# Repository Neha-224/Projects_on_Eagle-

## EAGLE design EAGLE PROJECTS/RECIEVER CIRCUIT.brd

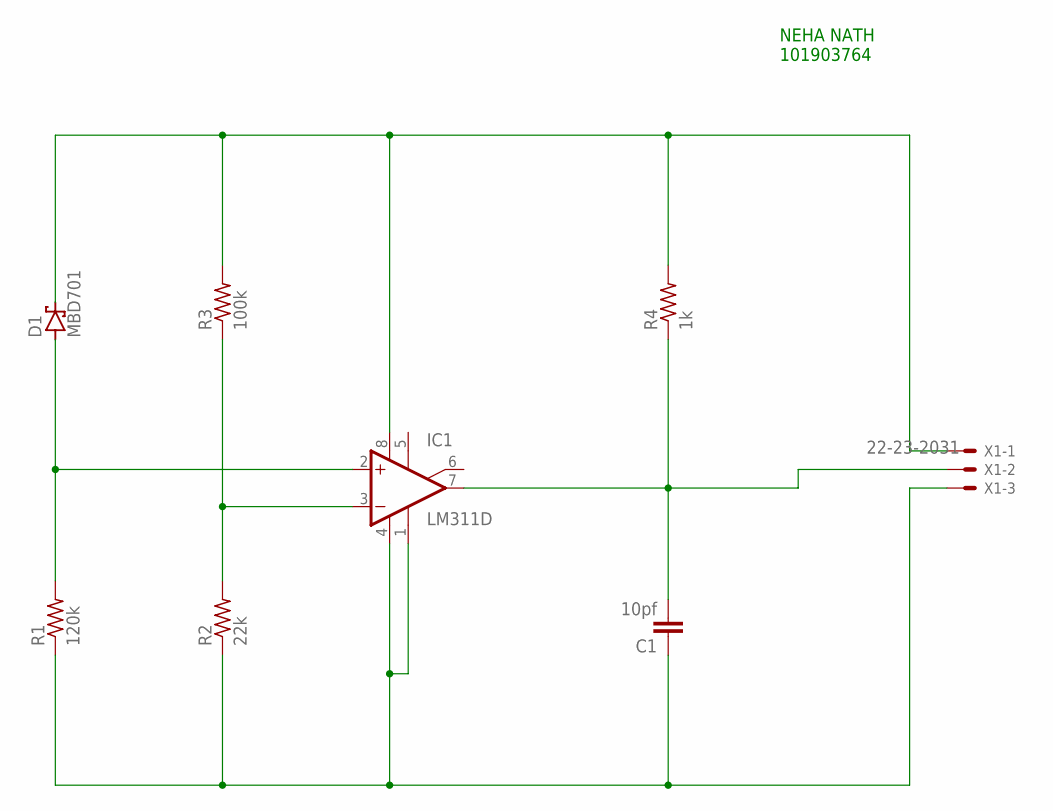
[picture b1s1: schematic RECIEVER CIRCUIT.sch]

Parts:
C1: 10pf; C2.5-4
D1: MBD701; TO92H
IC1: LM311D; SO08
R1: 120k; 0207/15
R2: 22k; 0207/15
R3: 100k; 0207/15
R4: 1k; 0207/15
X1: 22-23-2031

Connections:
unnamed: D1.2 (C), IC1.8 (V+), R3.2, R4.2, X1.1
unnamed: C1.1, IC1.1 (GND), IC1.4 (V-), R1.1, R2.1, X1.3
unnamed: D1.1 (A), IC1.2 (+IN), R1.2
unnamed: IC1.3 (-IN), R2.2, R3.1
unnamed: C1.2, IC1.7 (OUT), R4.1, X1.2

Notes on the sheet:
NEHA NATH 101903764

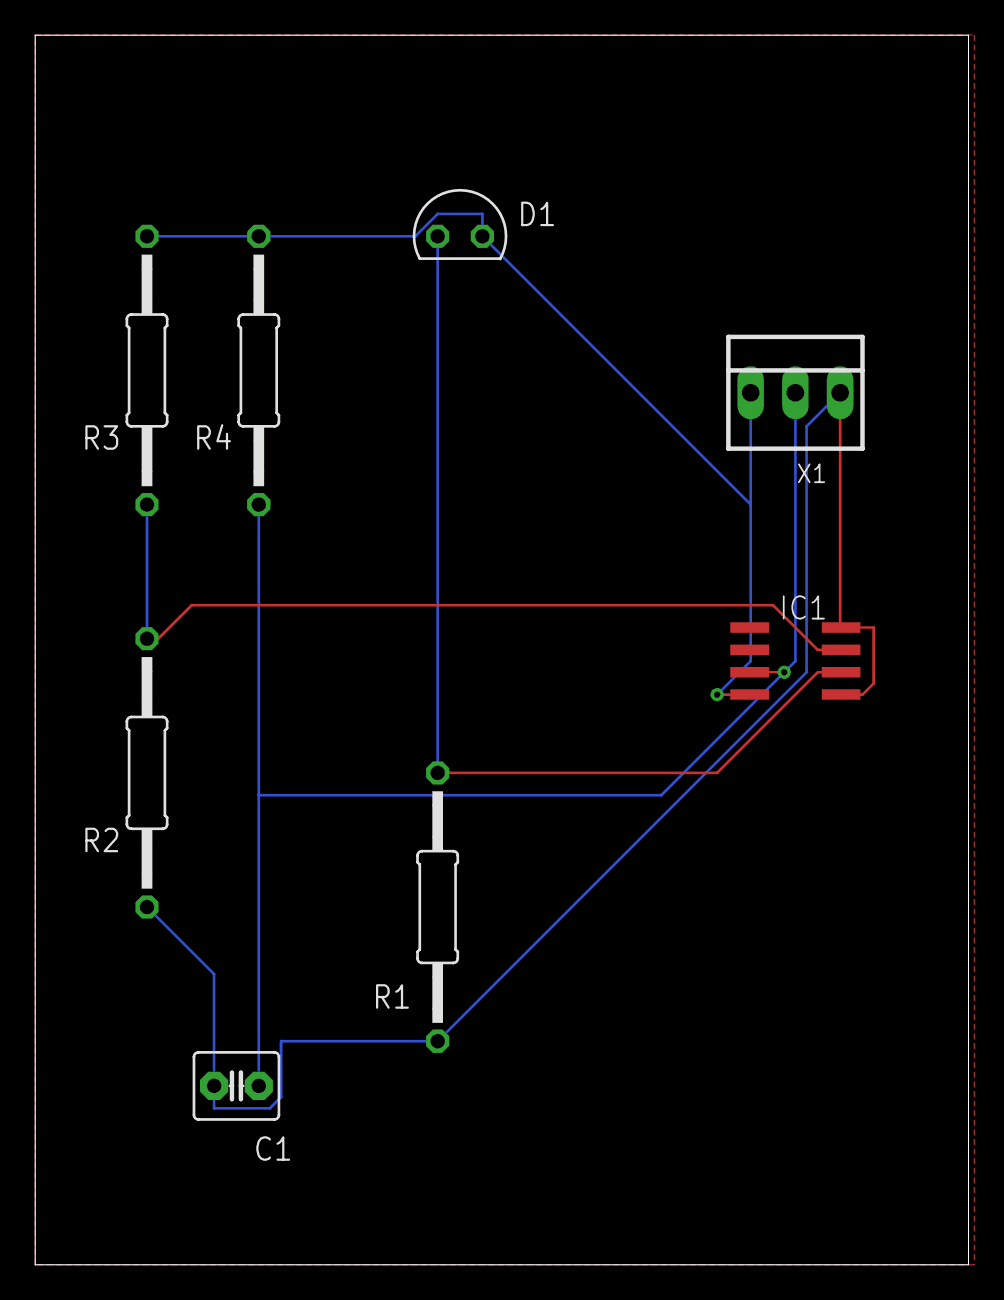
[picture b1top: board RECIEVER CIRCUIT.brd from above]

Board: 2 copper layers, 53.0 x 69.8 mm, 8 parts (0 on the bottom side), 5 nets.

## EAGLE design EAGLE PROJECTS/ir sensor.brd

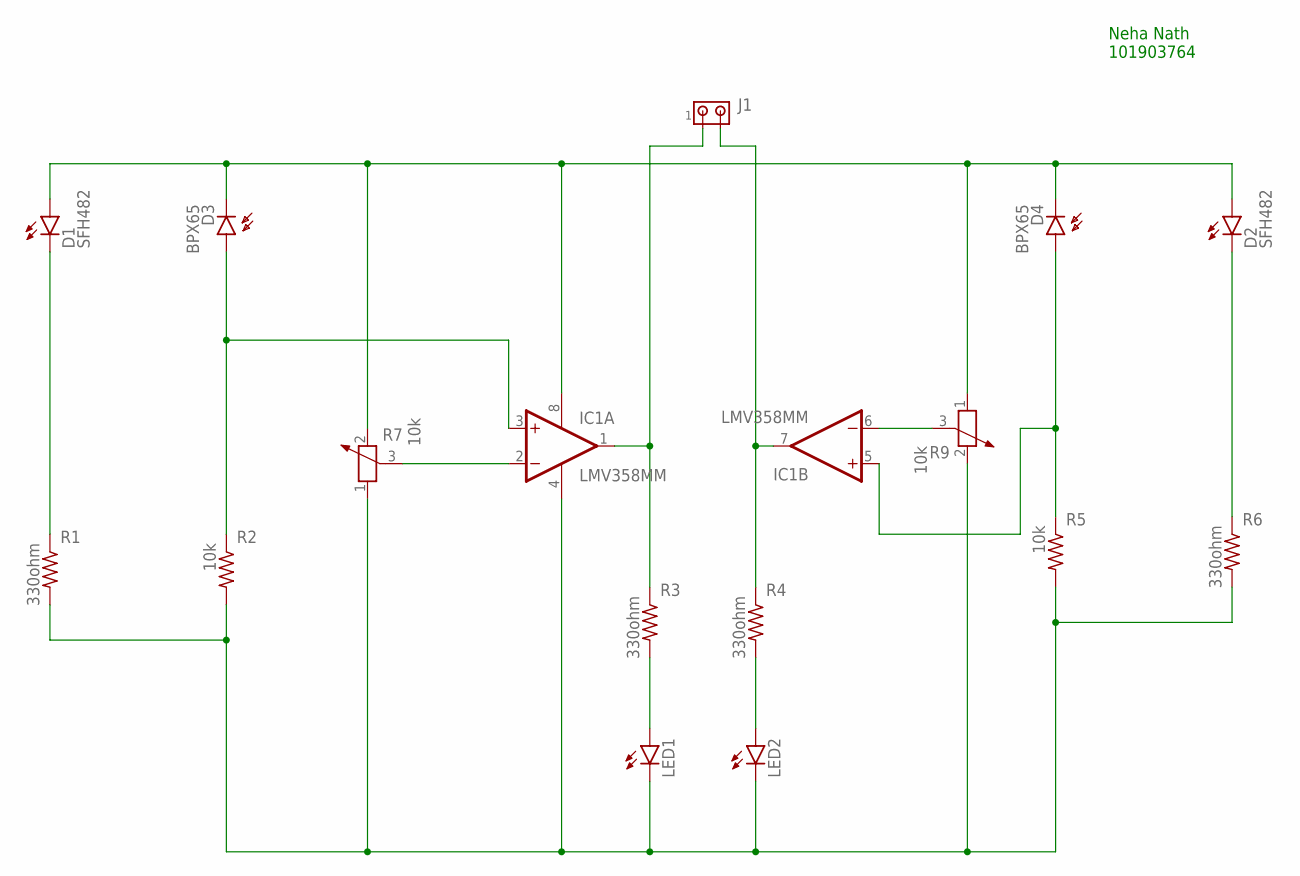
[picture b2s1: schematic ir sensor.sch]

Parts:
D1, D2: SFH482
D3, D4: BPX65
IC1: LMV358MM; MSOP08
J1: MTA02-100; 10X02MTA
LED1, LED2: LED3MM
R1, R3, R4, R6: 330ohm; 0207/10
R2, R5: 10k; 0207/10
R7, R9: 10k; PT-10S

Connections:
unnamed: D1.A, D2.A, D3.K (C), D4.K (C), IC1.8 (V+), R7.2, R9.1
unnamed: D1.K (C), R1.1
unnamed: IC1.4 (V-), LED1.K (C), LED2.K (C), R1.2, R2.2, R5.2, R6.2, R7.1, R9.2
unnamed: D3.A, IC1.3 (+IN), R2.1
unnamed: IC1.1 (OUT), J1.1, R3.1
unnamed: IC1.7 (OUT), J1.2, R4.1
unnamed: LED1.A, R3.2
unnamed: LED2.A, R4.2
unnamed: D4.A, IC1.5 (+IN), R5.1
unnamed: D2.K (C), R6.1
unnamed: IC1.6 (-IN), R9.3
unnamed: IC1.2 (-IN), R7.3

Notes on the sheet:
Neha Nath 101903764

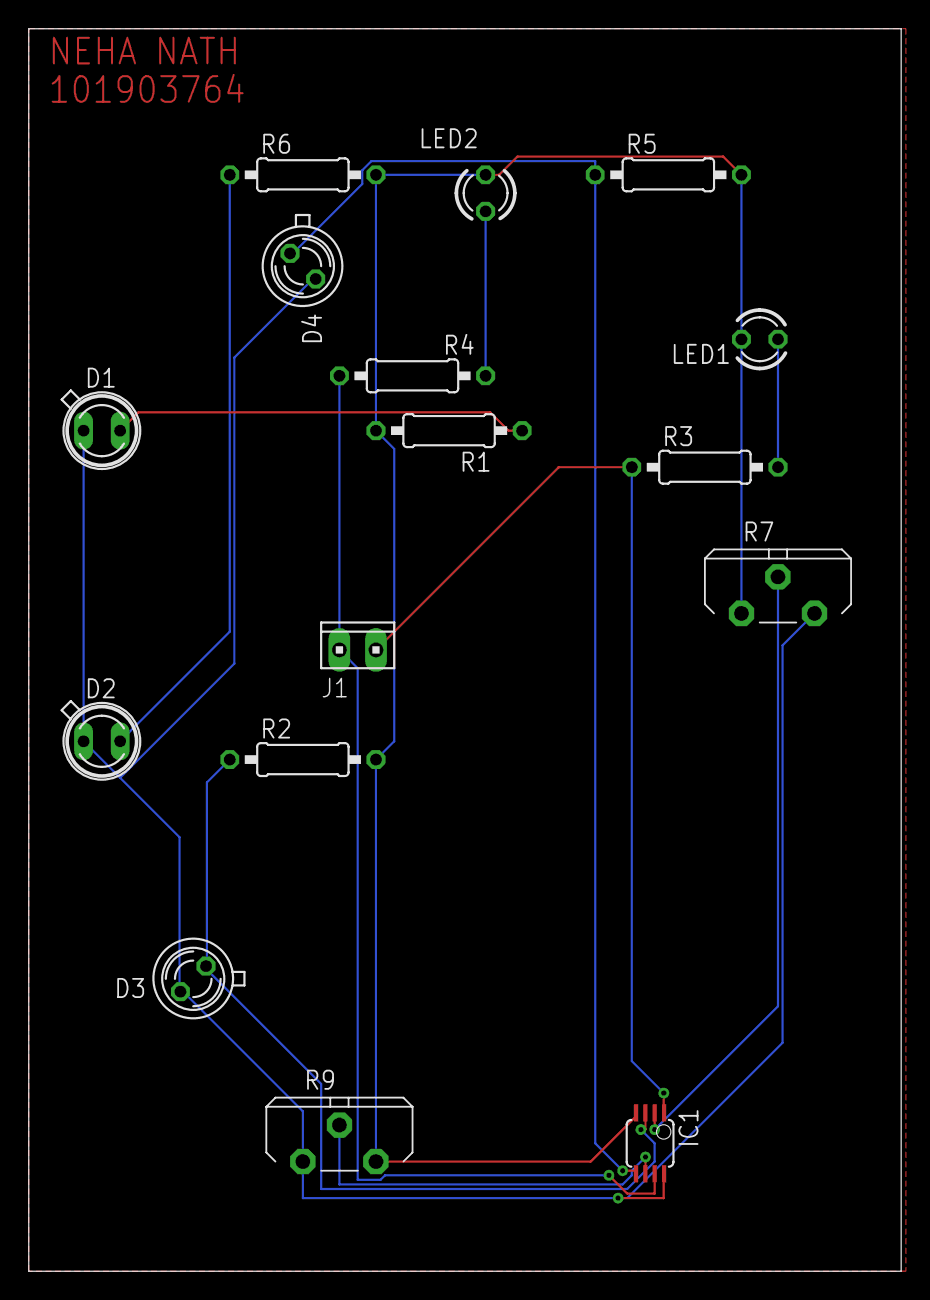
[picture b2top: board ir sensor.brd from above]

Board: 2 copper layers, 60.6 x 86.3 mm, 16 parts (0 on the bottom side), 12 nets.
